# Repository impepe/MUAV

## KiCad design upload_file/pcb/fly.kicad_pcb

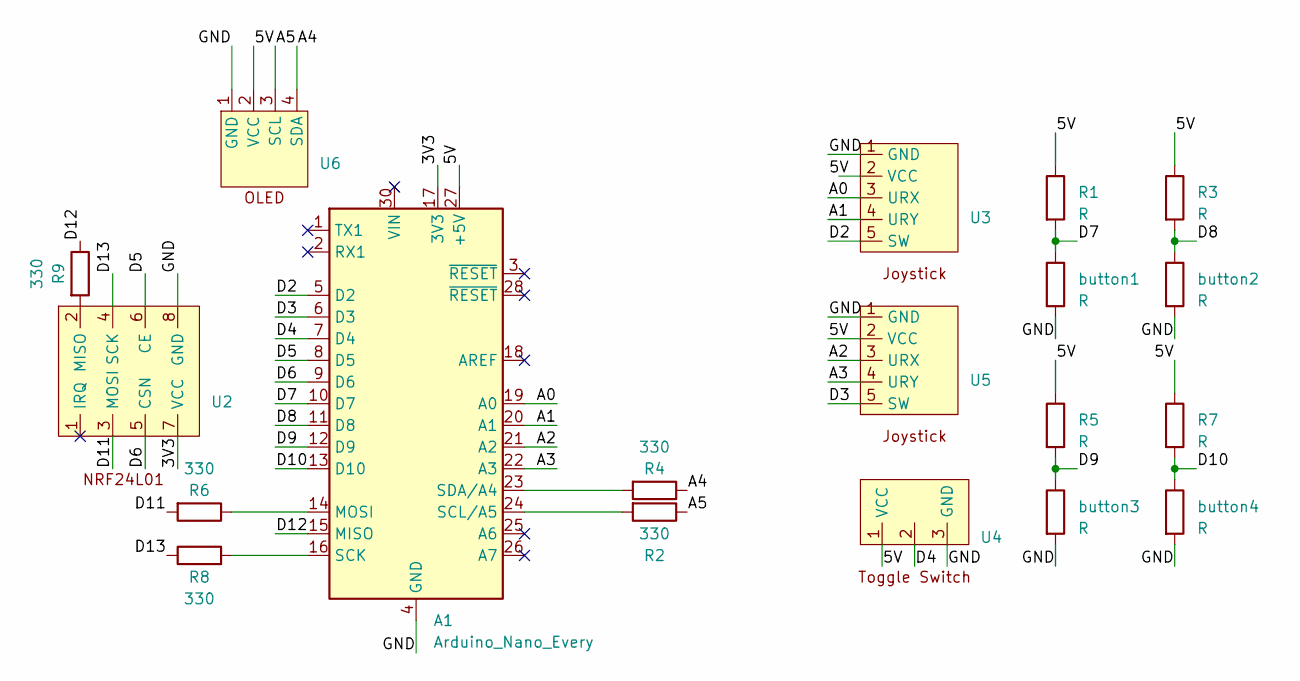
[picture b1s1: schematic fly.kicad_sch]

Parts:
A1: Arduino_Nano_Every; Arduino_Nano
R1, R3, R5, R7: R; R_1206_3216Metric_Pad1.30x1.75mm_HandSolder
R2, R4, R6, R8, R9: 330; R_1206_3216Metric_Pad1.30x1.75mm_HandSolder
U2: PinHeader_2x04_P2.54mm_Vertical
U3, U5: PinHeader_1x05_P2.54mm_Vertical
U4: PinHeader_1x03_P2.54mm_Vertical
U6: PinHeader_1x04_P2.54mm_Vertical
button1, button2, button3, button4: R; SW_CW_GPTS203211B

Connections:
/3V3: A1.17 (3V3), U2.7 (VCC)
/5V: A1.27 (+5V), R1.1, R3.1, R5.1, R7.1, U3.2 (VCC), U4.1 (VCC), U5.2 (VCC), U6.2 (VCC)
/A1: A1.20 (A1), U3.4 (URY)
/A2: A1.21 (A2), U5.3 (URX)
/A3: A1.22 (A3), U5.4 (URY)
/A4: R4.1, U6.4 (SDA)
/A5: R2.1, U6.3 (SCL)
/D2: A1.5 (D2), U3.5 (SW)
/D3: A1.6 (D3), U5.5 (SW)
/D4: A1.7 (D4), U4.2
/D5: A1.8 (D5), U2.6 (CE)
/D6: A1.9 (D6), U2.5 (CSN)
/D7: A1.10 (D7), R1.2, button1.1
/D8: A1.11 (D8), R3.2, button2.1
/D9: A1.12 (D9), R5.2, button3.1
/D10: A1.13 (D10), R7.2, button4.1
/D11: R6.2, U2.3 (MOSI)
/D12: A1.15 (MISO), R9.1
/D13: R8.1, U2.4 (SCK)
/GND: A1.4 (GND), A1.29 (GND), U2.8 (GND), U3.1 (GND), U4.3 (GND), U5.1 (GND), U6.1 (GND), button1.2, button2.2, button3.2, button4.2
A0: A1.19 (A0), U3.3 (URX)
unnamed: A1.14 (MOSI), R6.1
unnamed: A1.16 (SCK), R8.2
unnamed: A1.24 (SCL/A5), R2.2
unnamed: A1.23 (SDA/A4), R4.2
unnamed: R9.2, U2.2 (MISO)

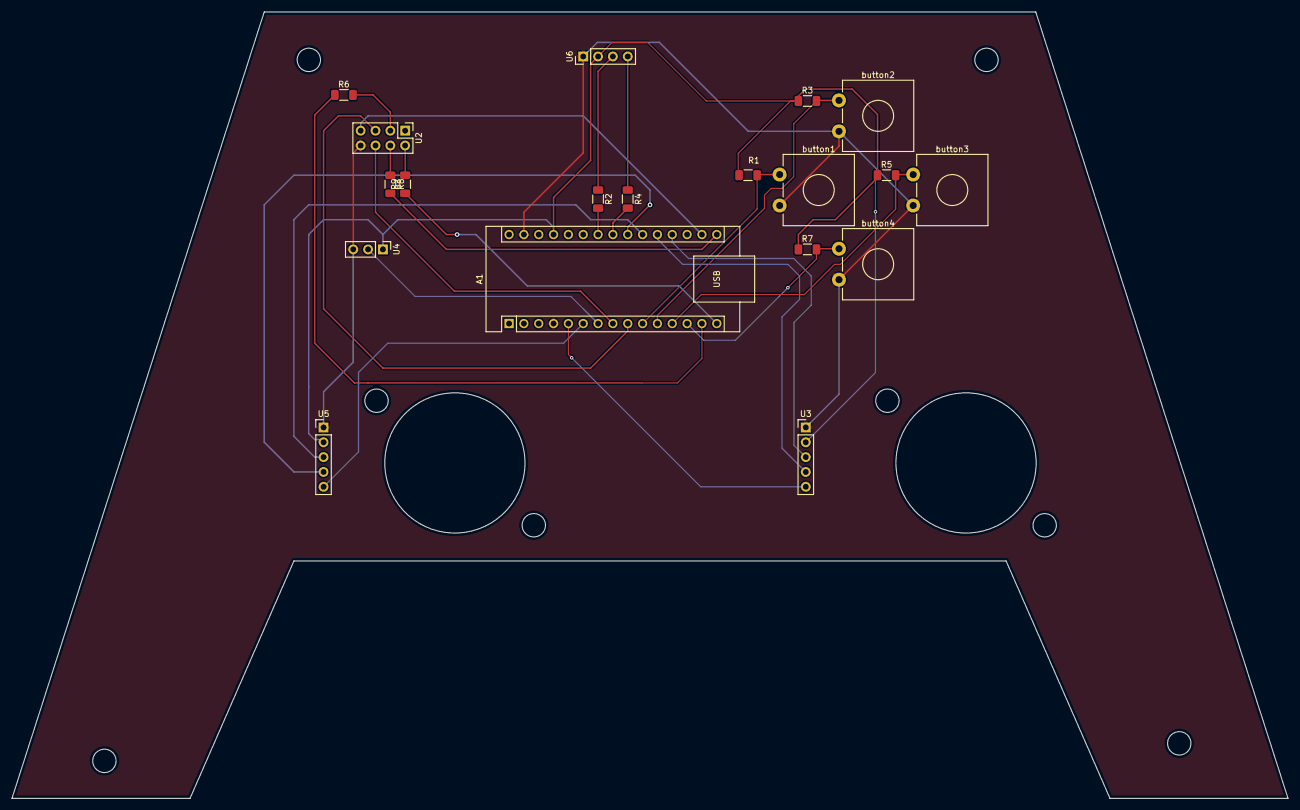
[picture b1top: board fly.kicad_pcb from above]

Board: 2 copper layers, 218.4 x 134.6 mm, 19 parts (0 on the bottom side), 26 nets.

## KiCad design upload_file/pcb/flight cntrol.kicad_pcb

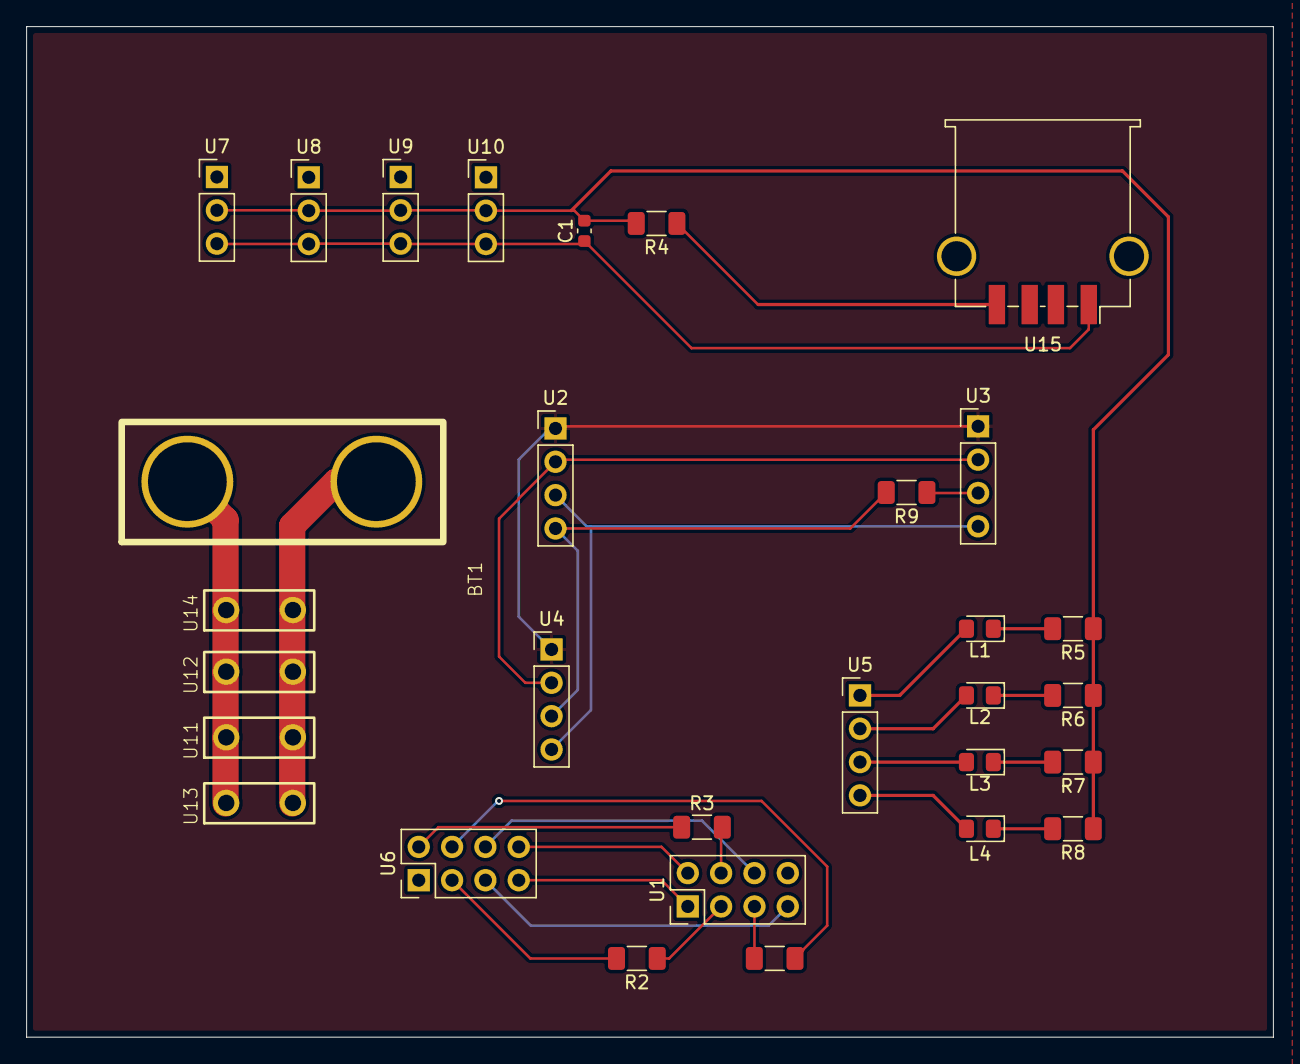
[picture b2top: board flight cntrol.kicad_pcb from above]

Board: 2 copper layers, 95.0 x 77.0 mm, 30 parts (0 on the bottom side), 26 nets.

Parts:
BT1: Battery; awg10
C1: C; C_0603_1608Metric
L1, L2, L3, L4: R; LED_0805_2012Metric_Pad1.15x1.40mm_HandSolder
R1, R2, R3, R4, R5, R6, R7, R8, R9: R; R_1206_3216Metric_Pad1.30x1.75mm_HandSolder
U1, U6: PinHeader_2x04_P2.54mm_Vertical
U2, U3, U4, U5: PinHeader_1x04_P2.54mm_Vertical
U7, U8, U9, U10: PinHeader_1x03_P2.54mm_Vertical
U11, U12, U13, U14: eso_power
U15: USB_A_TE_292303-7_Horizontal

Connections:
/CE0: U1.6 (CE0), U6.6 (CE)
/CE1: U1.7 (CE1), U6.5 (CSN)
/GND: U2.1 (GND), U3.1 (GND), U4.1 (GND)
/LED1: L1.2, U5.1 (led1)
/LED2: L2.2, U5.2 (led2)
/LED3: L3.2, U5.3 (led3)
/LED4: L4.2, U5.4 (led4)
/POWER_VCC: BT1.1 (+), BT1.2 (-), C1.1, U7.3 (GND), U8.3 (GND), U9.3 (GND), U10.3 (GND), U11.1 (vcc), U11.2 (gnd), U12.1 (vcc), U12.2 (gnd), U13.1 (vcc), U13.2 (gnd), U14.1 (vcc), U14.2 (gnd), U15.1 (GND)
/RASP_SPI_CLK: R1.1, U6.4 (SCK)
/RASP_SPI_GND: U1.2 (gnd), U6.8 (GND)
/RASP_SPI_MISO: R3.2, U1.4 (MISO)
/RASP_SPI_MOSI: R2.2, U6.3 (MOSI)
/RASP_SPI_VCC: U1.1 (vcc), U6.7 (VCC)
/SCL: R9.2, U2.4 (SCL), U4.3 (SCL)
/SDA: U2.3 (SDA), U3.4 (SDA), U4.4 (SDA)
/USB_VCC: C1.2, R4.2, R5.1, R6.1, R7.1, R8.1, U7.2 (vcc), U8.2 (vcc), U9.2 (vcc), U10.2 (vcc)
/VCC: U2.2 (VCC), U3.2 (VCC), U4.2 (VCC)
unnamed: L1.1, R5.2
unnamed: L2.1, R6.2
unnamed: L3.1, R7.2
unnamed: L4.1, R8.2
unnamed: R1.2, U1.5 (CLK)
unnamed: R2.1, U1.3 (MOSI)
unnamed: R9.1, U3.3 (SCL)
unnamed: R3.1, U6.2 (MISO)
unnamed: R4.1, U15.4 (VCC)

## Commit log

2023-05-01 test
2023-05-11 by_pepe
2023-08-20 update by pepe
